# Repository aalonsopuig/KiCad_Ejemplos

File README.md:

# KiCad_Ejemplos_1
 Ejemplos de circuitos utilizados en las clases que imparto en la universidad

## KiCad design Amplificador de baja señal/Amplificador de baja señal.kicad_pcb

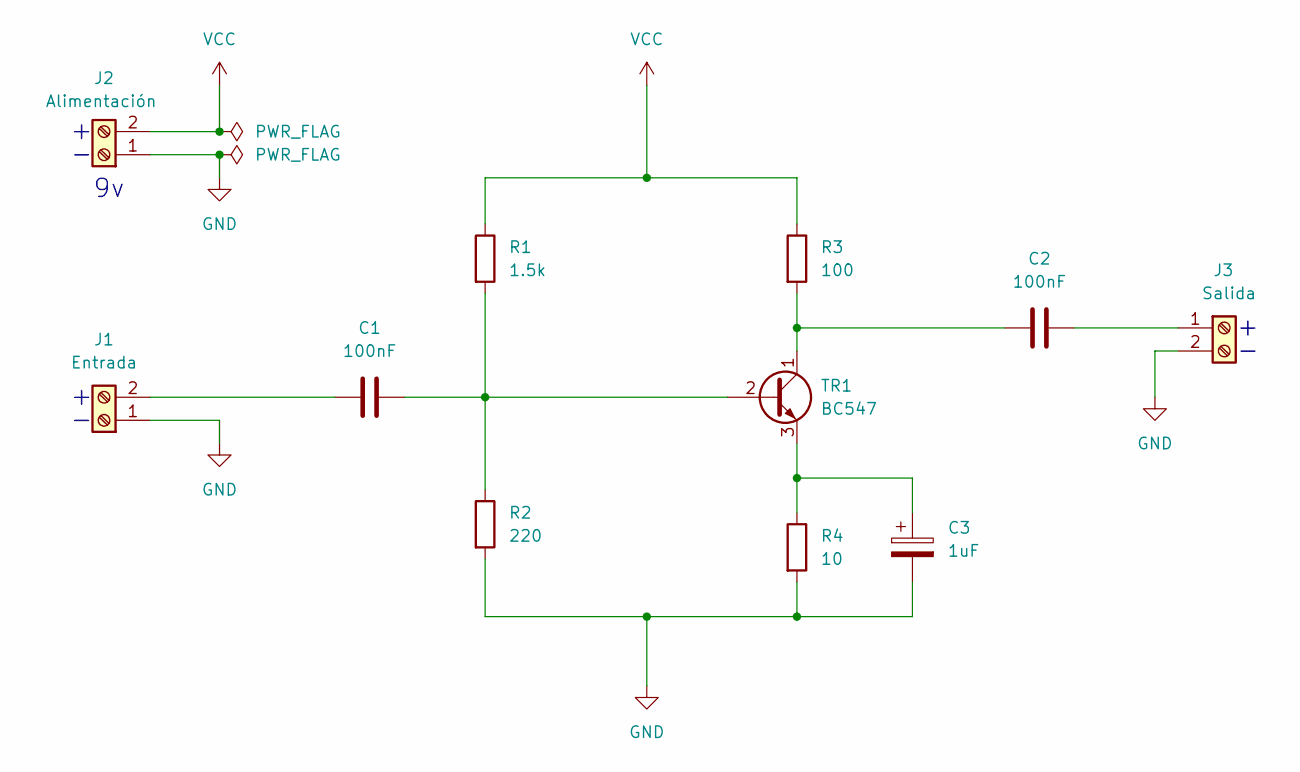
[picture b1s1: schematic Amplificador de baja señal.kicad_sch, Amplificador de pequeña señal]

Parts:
C1, C2: 100nF; C_Disc_D7.5mm_W2.5mm_P5.00mm
C3: 1uF; C_Radial_D4.0mm_H7.0mm_P1.50mm
J1: Entrada; TerminalBlock_Phoenix_PT-1,5-2-5.0-H_1x02_P5.00mm_Horizontal
J2: Alimentación; TerminalBlock_Phoenix_PT-1,5-2-5.0-H_1x02_P5.00mm_Horizontal
J3: Salida; TerminalBlock_Phoenix_PT-1,5-2-5.0-H_1x02_P5.00mm_Horizontal
R1: 1.5k; R_Axial_DIN0207_L6.3mm_D2.5mm_P10.16mm_Horizontal
R2: 220; R_Axial_DIN0207_L6.3mm_D2.5mm_P10.16mm_Horizontal
R3: 100; R_Axial_DIN0207_L6.3mm_D2.5mm_P10.16mm_Horizontal
R4: 10; R_Axial_DIN0207_L6.3mm_D2.5mm_P10.16mm_Horizontal
TR1: BC547; TO-92_Inline

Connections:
GND: C3.2, J1.1, J2.1, J3.2, R2.2, R4.2
unnamed: C1.2, J1.2
unnamed: C2.1, J3.1
unnamed: C1.1, R1.2, R2.1, TR1.2 (B)
unnamed: C2.2, R3.2, TR1.1 (C)
unnamed: C3.1, R4.1, TR1.3 (E)
VCC: J2.2, R1.1, R3.1

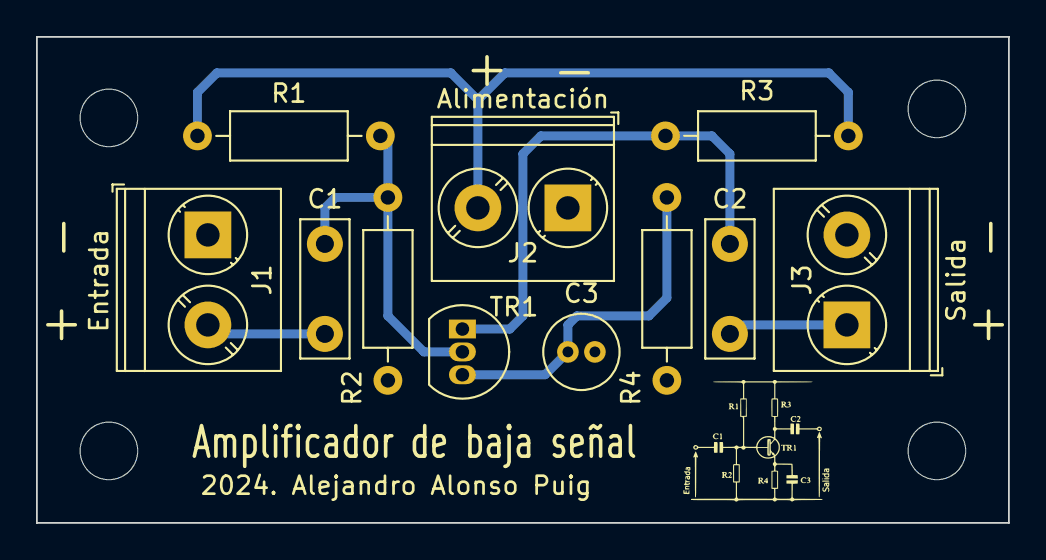
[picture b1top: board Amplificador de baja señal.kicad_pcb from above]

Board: 2 copper layers, 54.0 x 27.0 mm, 11 parts (0 on the bottom side), 7 nets.

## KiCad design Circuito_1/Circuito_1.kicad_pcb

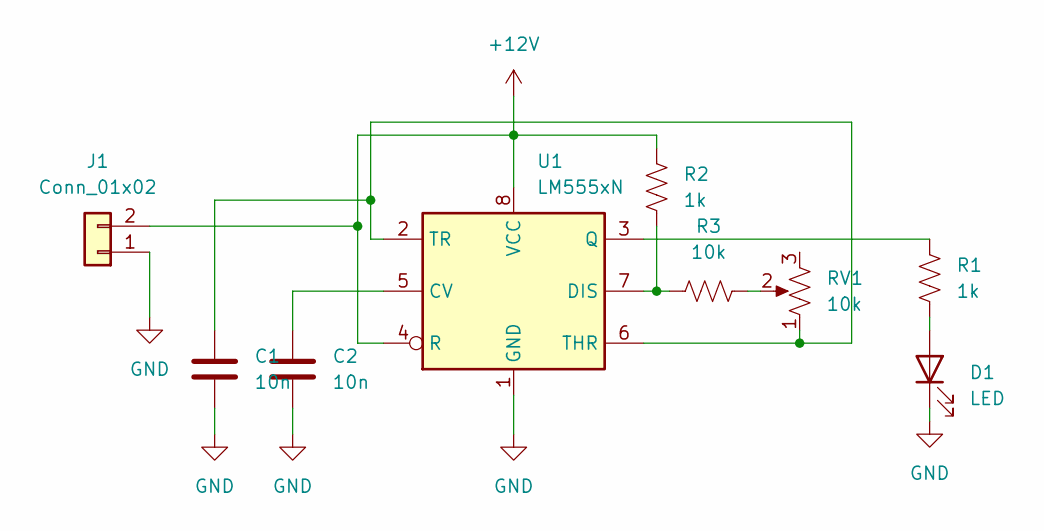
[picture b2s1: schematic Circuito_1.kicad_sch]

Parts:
C1, C2: 10n; C_Rect_L7.0mm_W2.5mm_P5.00mm
D1: LED; LED_D5.0mm
J1: Conn_01x02; Molex_KK-254_AE-6410-02A_1x02_P2.54mm_Vertical
R1, R2: 1k; R_Axial_DIN0207_L6.3mm_D2.5mm_P10.16mm_Horizontal
R3: 10k; R_Axial_DIN0207_L6.3mm_D2.5mm_P10.16mm_Horizontal
RV1: 10k; Potentiometer_ACP_CA9-V10_Vertical
U1: LM555xN; DIP-8_W7.62mm

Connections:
+12V: J1.2, R2.2, U1.4 (R), U1.8 (VCC)
GND: C1.2, C2.2, D1.1 (K), J1.1, U1.1 (GND)
unnamed: D1.2 (A), R1.1
unnamed: R3.1, RV1.2
unnamed: C2.1, U1.5 (CV)
unnamed: R2.1, R3.2, U1.7 (DIS)
unnamed: R1.2, U1.3 (Q)
unnamed: C1.1, RV1.1, U1.2 (TR), U1.6 (THR)

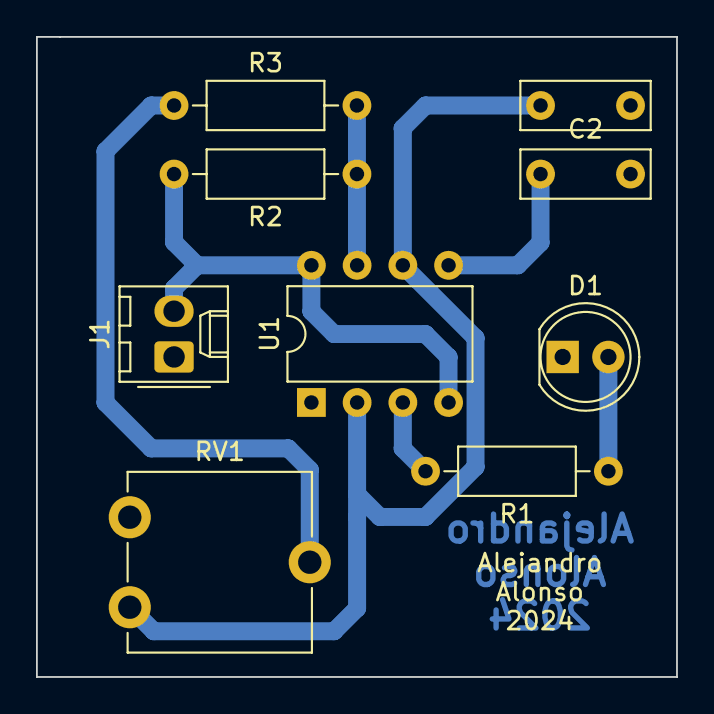
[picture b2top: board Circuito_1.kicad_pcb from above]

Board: 2 copper layers, 35.6 x 35.6 mm, 9 parts (0 on the bottom side), 8 nets.

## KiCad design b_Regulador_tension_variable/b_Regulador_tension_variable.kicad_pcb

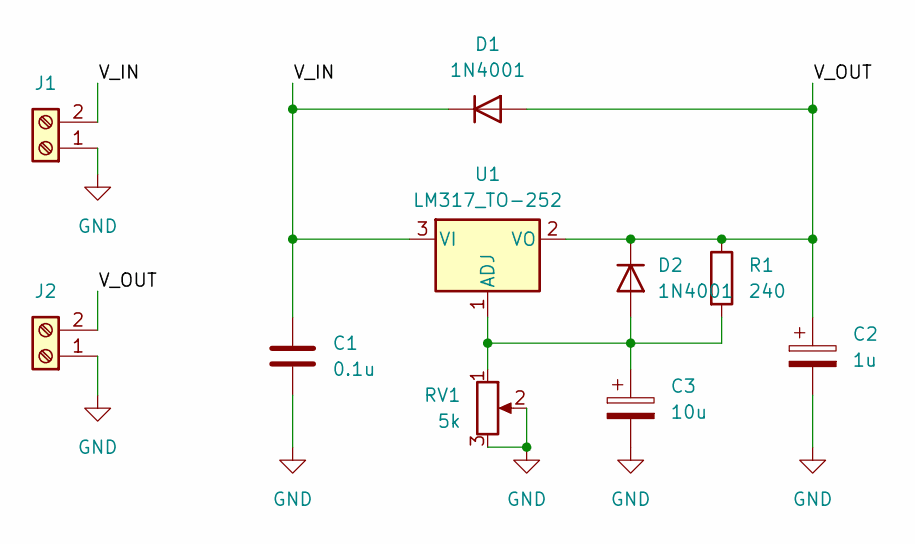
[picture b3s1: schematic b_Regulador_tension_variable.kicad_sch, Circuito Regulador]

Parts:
C1: 0.1u; C_0201_0603Metric
C2: 1u; CP_Elec_6.3x5.8
C3: 10u; CP_Elec_6.3x5.8
D1, D2: 1N4001; D_SMA
J1, J2: Screw_Terminal_01x02; TerminalBlock_Phoenix_MKDS-1,5-2_1x02_P5.00mm_Horizontal
R1: 240; R_1206_3216Metric
RV1: 5k; Potentiometer_Bourns_3296W_Vertical
U1: LM317_TO-252; TO-252-2

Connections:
/V_IN: C1.1, D1.1 (K), J1.2, U1.3 (VI)
/V_OUT: C2.1, D1.2 (A), D2.1 (K), J2.2, R1.1, U1.2 (VO)
GND: C1.2, C2.2, C3.2, J1.1, J2.1, RV1.2, RV1.3
unnamed: C3.1, D2.2 (A), R1.2, RV1.1, U1.1 (ADJ)

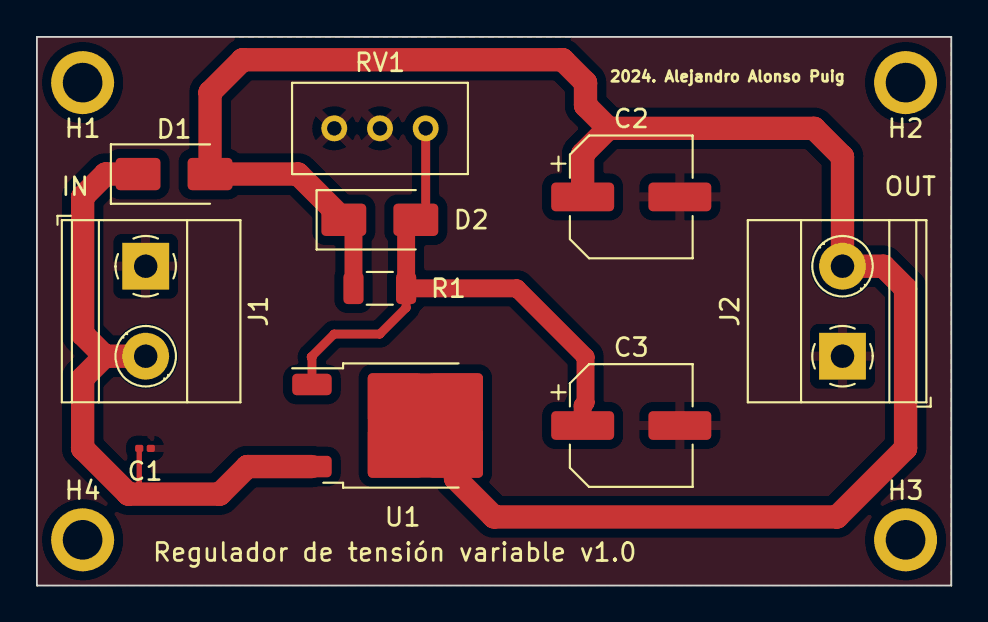
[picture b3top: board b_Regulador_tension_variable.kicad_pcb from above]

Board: 2 copper layers, 50.8 x 30.5 mm, 14 parts (0 on the bottom side), 4 nets.

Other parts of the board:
H1, H2, H3, H4: MountingHole_2.2mm_M2_ISO7380_Pad
